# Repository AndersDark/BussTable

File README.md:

# BussTable

This code uses an ESP8266 connected with a 16x2 LCD display to show the time till next buss arrives at a specific buss stop.

It uses entur api

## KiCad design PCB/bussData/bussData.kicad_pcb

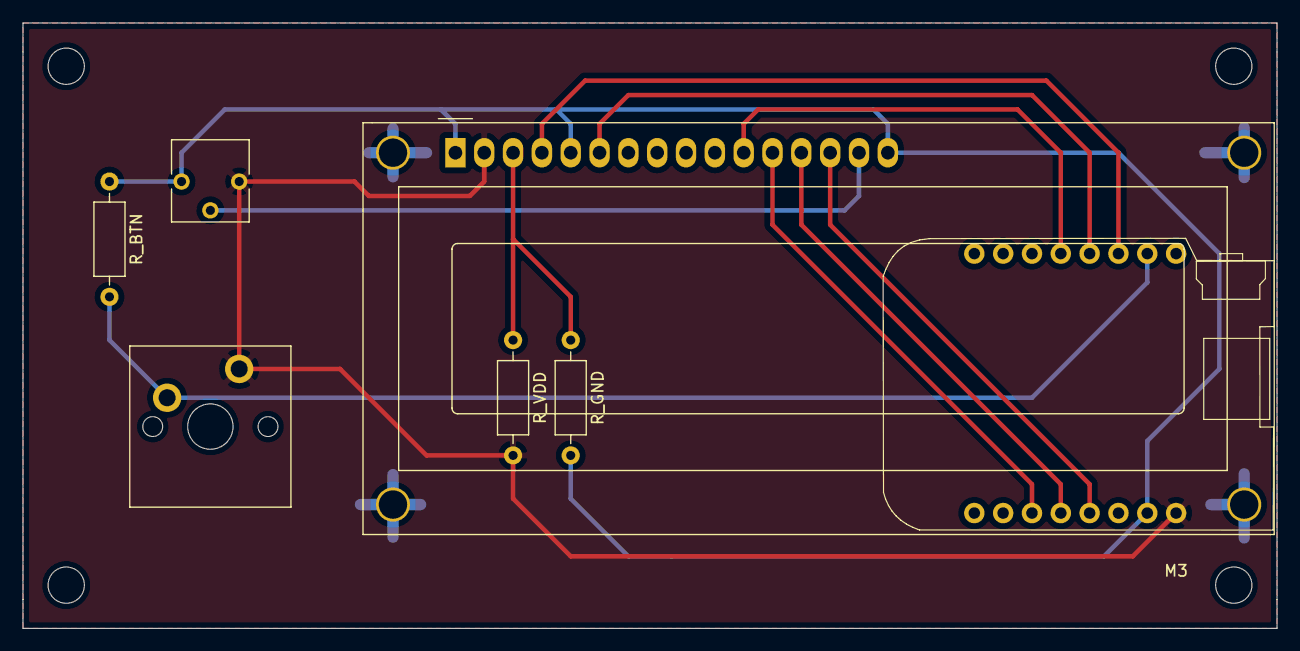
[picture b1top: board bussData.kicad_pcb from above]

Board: 2 copper layers, 110.5 x 53.3 mm, 8 parts (0 on the bottom side), 11 nets.

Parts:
DIM1: R_POT_TRIM; Potentiometer_Vishay_T73YP_Vertical
LCD1: RC1602A; WC1602A
M3: MountingHole_3.2mm_M3
R_BTN: ?; R_Axial_DIN0207_L6.3mm_D2.5mm_P10.16mm_Horizontal
R_GND: ?; R_Axial_DIN0207_L6.3mm_D2.5mm_P10.16mm_Horizontal
R_VDD: ?; R_Axial_DIN0207_L6.3mm_D2.5mm_P10.16mm_Horizontal
btn1: SW_Push_Open; SW_Cherry_MX_PCB_1.00u
esp8266 D1 Wemos mini: WeMos_mini; D1_mini_board

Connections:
unnamed: DIM1.1, LCD1.1, LCD1.5, LCD1.16, R_BTN.1, R_GND.2, esp8266 D1 Wemos mini.2
unnamed: DIM1.2, LCD1.15
unnamed: DIM1.3, LCD1.2, R_VDD.2, btn1.2, esp8266 D1 Wemos mini.1
unnamed: LCD1.3, R_GND.1, R_VDD.1
unnamed: LCD1.4, esp8266 D1 Wemos mini.14
unnamed: LCD1.6, esp8266 D1 Wemos mini.13
unnamed: LCD1.11, esp8266 D1 Wemos mini.12
unnamed: LCD1.12, esp8266 D1 Wemos mini.6
unnamed: LCD1.13, esp8266 D1 Wemos mini.5
unnamed: LCD1.14, esp8266 D1 Wemos mini.4
unnamed: R_BTN.2, btn1.1, esp8266 D1 Wemos mini.15

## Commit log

2021-09-10 change .gitignore
2021-10-04 changed API request to using WiFiCleintSecure
2021-10-04 Chenged pins
2021-10-04 deleted unnecessary files
2021-10-12 added pcb
2021-10-16 updated the PCB
2021-10-16 it dosen't work yet
2021-11-08 updated pcb
2021-11-08 PCB done
2021-11-27 Time now works instantly, cleaned the code
